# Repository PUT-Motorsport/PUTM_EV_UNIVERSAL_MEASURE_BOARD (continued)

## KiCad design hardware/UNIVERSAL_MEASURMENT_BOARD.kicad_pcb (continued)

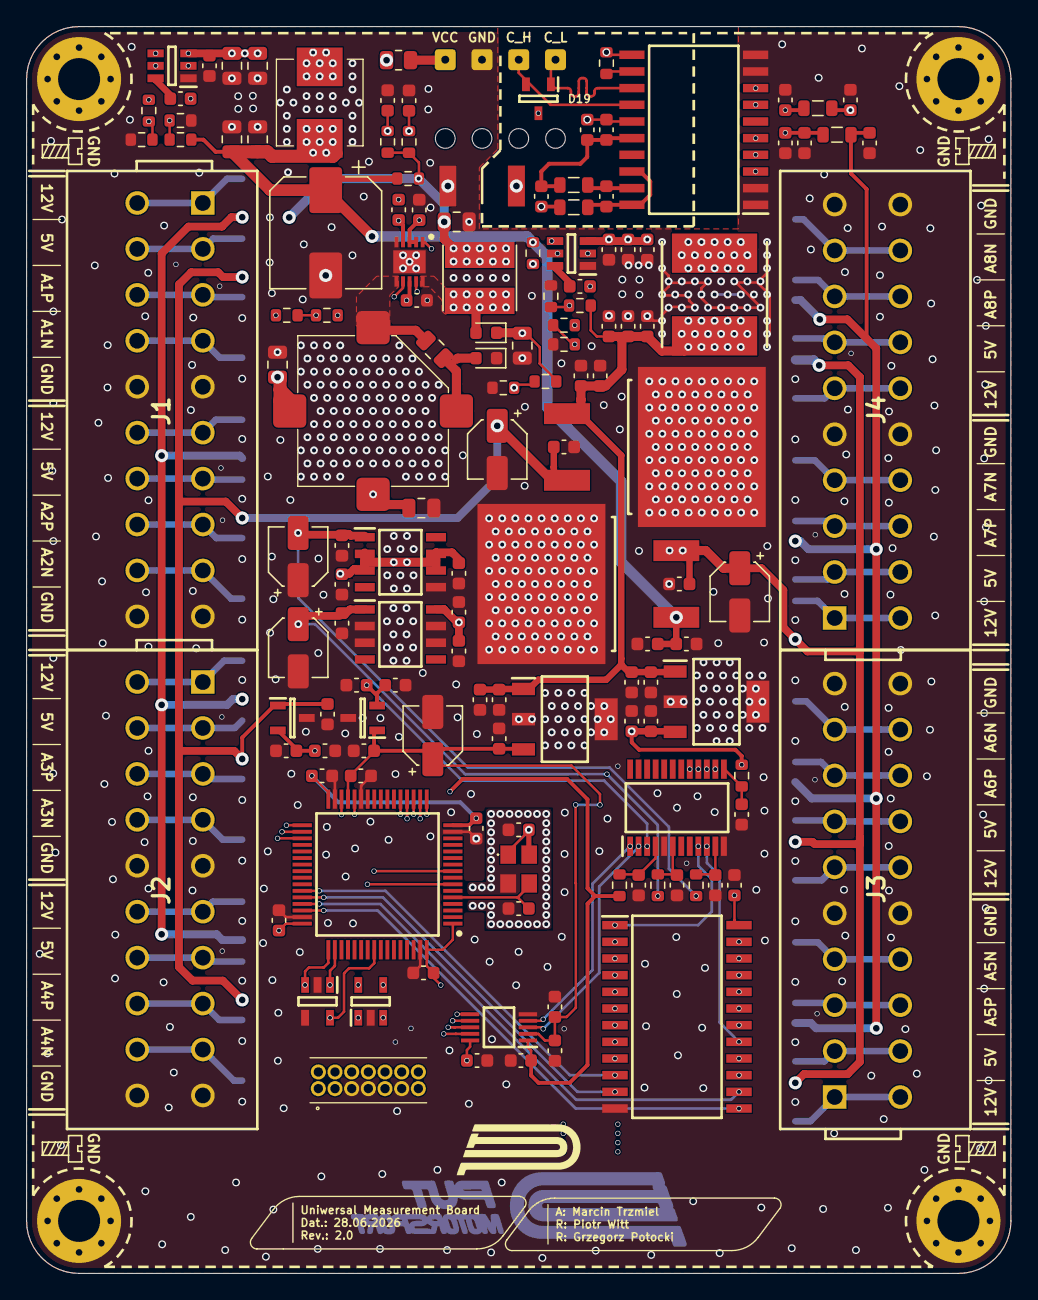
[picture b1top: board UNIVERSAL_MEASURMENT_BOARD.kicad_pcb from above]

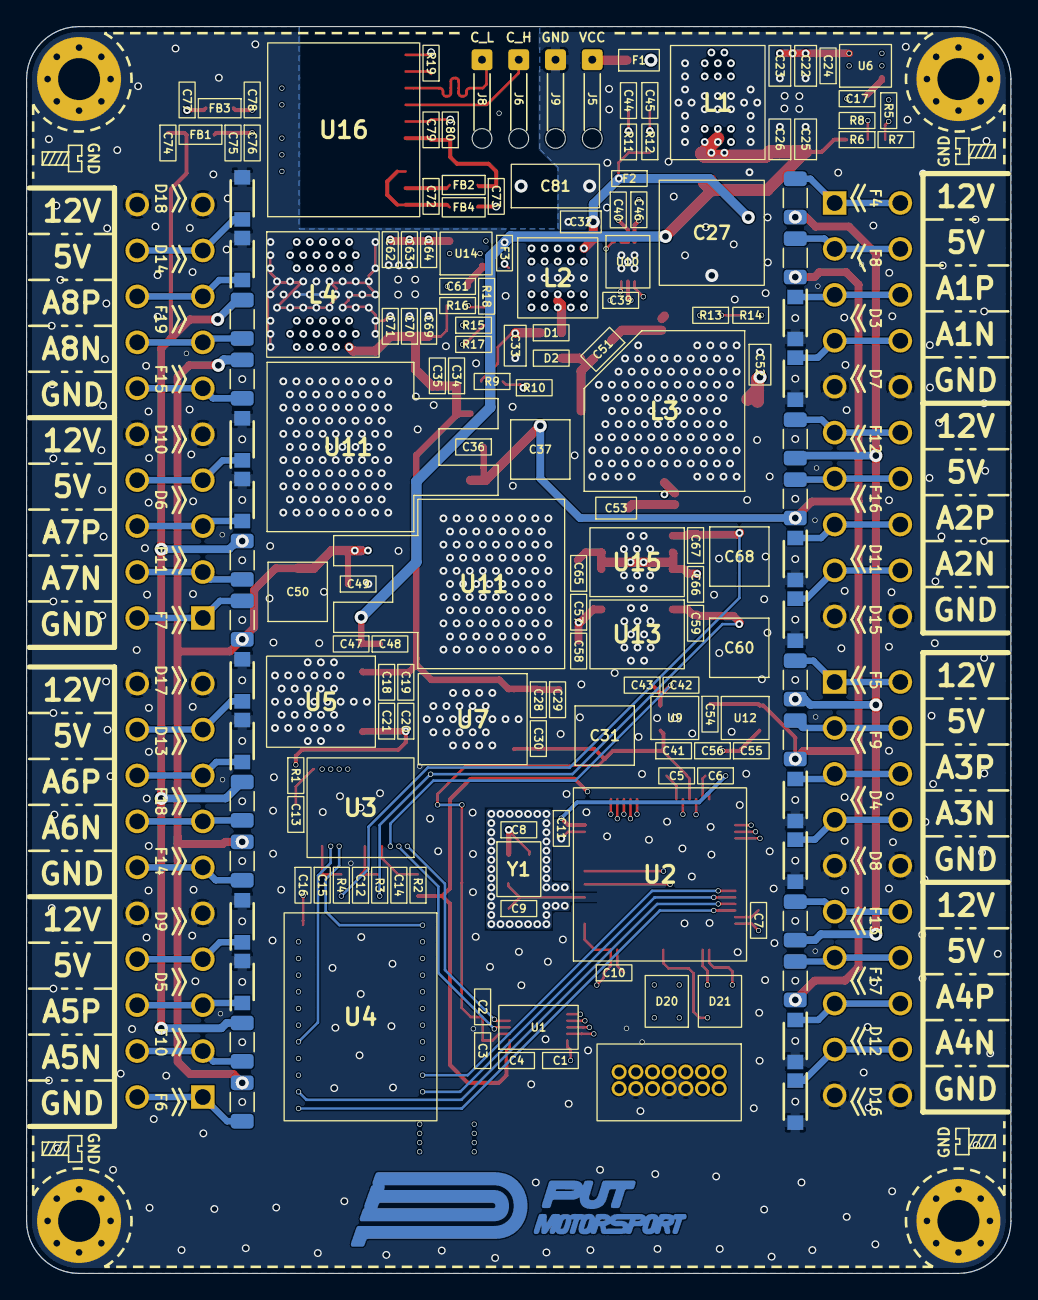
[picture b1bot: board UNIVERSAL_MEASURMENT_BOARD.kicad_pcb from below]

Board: 6 copper layers, 75.0 x 95.0 mm, 173 parts (36 on the bottom side), 101 nets.

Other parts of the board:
C1, C2, C4, C5, C6, C7, C8, C10, C11: 100nF; C_0603_1608Metric
C3: 10nF; C_0603_1608Metric
C9: 10pF; C_0603_1608Metric
U1: ADS8863IDGS; SOP50P490X110-10N
U2: STM32G484RET3; QFP50P1200X1200X160-64N
Y1: ATX-H11-F-16.000MHz-G100-T; ATXH11F16000MHzG100T

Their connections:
+3V0A: C4.1, U1.1 (REF), U2.28 (VREF+); also elsewhere on the board
+3V3: C1.1, C6.1, C7.1, C8.1, C10.1, C11.1, U1.10 (DVDD), U2.1 (VBAT), U2.16 (VDD), U2.32 (VDD), U2.48 (VDD), U2.64 (VDD), Y1.1 (~INH), Y1.4 (VDD); also elsewhere on the board
+3V3A: C2.1, C3.1, C5.1, U1.2 (AVDD), U2.29 (VDDA); also elsewhere on the board
/can/CAN_RX: U2.35 (FDCAN2_TX); also elsewhere on the board
/can/CAN_STB: U2.33 (PB11); also elsewhere on the board
/can/CAN_TX: U2.34 (FDCAN2_RX); also elsewhere on the board
/connectors/NRST: U2.7 (PG10); also elsewhere on the board
/connectors/SWCLK: U2.50 (SYS_JTCK-SWCLK); also elsewhere on the board
/connectors/SWDIO: U2.49 (SYS_JTMS-SWDIO); also elsewhere on the board
/connectors/SWO: U2.56 (SYS_JTDO-SWO); also elsewhere on the board
/connectors/UART_RX_PROG: U2.30 (LPUART1_RX); also elsewhere on the board
/connectors/UART_TX_PROG: U2.9 (LPUART1_TX); also elsewhere on the board
/mcu & adc/ADCCS: U1.6 (~CS), U2.18 (PA4)
/mcu & adc/ADDR1: U2.43 (PA9); also elsewhere on the board
/mcu & adc/ADDR2: U2.44 (PA10); also elsewhere on the board
/mcu & adc/ADDR3: U2.45 (PA11); also elsewhere on the board
/mcu & adc/AINN: U1.4 (AINN); also elsewhere on the board
/mcu & adc/AINP: U1.3 (AINP); also elsewhere on the board
/mcu & adc/HSE: C9.1, U2.5 (RCC_OSC_IN), Y1.3 (OUTPUT)
/mcu & adc/MISO: U1.9 (MISO), U2.20 (SPI1_MISO); also elsewhere on the board
/mcu & adc/MOSI: U1.7 (MOSI), U2.21 (SPI1_MOSI); also elsewhere on the board
/mcu & adc/MUXEN: U2.46 (PA12); also elsewhere on the board
/mcu & adc/PGACS: U2.17 (PA3); also elsewhere on the board
/mcu & adc/SCLK: U1.8 (SCLK), U2.19 (SPI1_SCK); also elsewhere on the board
GND: C1.2, C2.2, C3.2, C4.2, C5.2, C6.2, C7.2, C8.2, C9.2, C10.2, C11.2, U1.5 (GND), U2.15 (VSS), U2.27 (VSSA), U2.31 (VSS), U2.47 (VSS), U2.63 (VSS), Y1.2 (GND); also elsewhere on the board

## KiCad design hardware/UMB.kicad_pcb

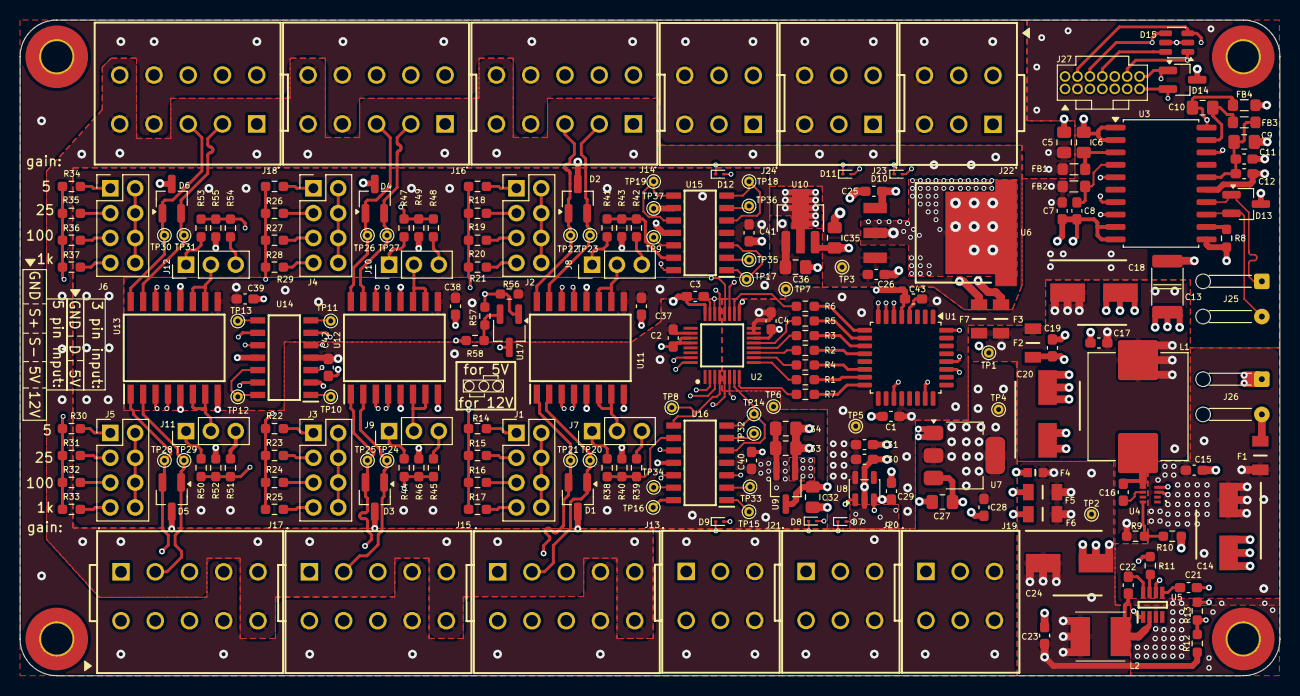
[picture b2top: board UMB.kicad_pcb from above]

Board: 6 copper layers, 128.8 x 67.0 mm, 214 parts (0 on the bottom side), 149 nets.

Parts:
C1, C2, C4, C7, C11, C15, C16, C19, C22, C30, C37, C38, C39, C40, C41, C42, C43: 100n; C_0603_1608Metric_Pad1.08x0.95mm_HandSolder
C3, C29, C31: 1u; C_0603_1608Metric_Pad1.08x0.95mm_HandSolder
C5, C6, C9, C10: 47u; C_0805_2012Metric_Pad1.18x1.45mm_HandSolder
C8, C12: 10n; C_0603_1608Metric_Pad1.08x0.95mm_HandSolder
C13: 4.7nF/Y2; CAPC5728X280N
C14, C18, C20, C24: 10u; CAPAE660X600N
C17, C23, C26, C28: 22u; C_0603_1608Metric_Pad1.08x0.95mm_HandSolder
C21: 8.2n; C_0603_1608Metric_Pad1.08x0.95mm_HandSolder
C25: 470n; C_0603_1608Metric_Pad1.08x0.95mm_HandSolder
C27, C33: 10u; C_0805_2012Metric_Pad1.18x1.45mm_HandSolder
C32, C34, C35, C36: 2.2u; C_0805_2012Metric_Pad1.18x1.45mm_HandSolder
D1, D2, D3, D4, D5, D6: CPDT-12V; SOT-23_Handsoldering
D7, D8, D9, D10, D11, D12: SZESD9101P2T5G; D_SOD-923
D13, D14: STS232050B751; SOT-23_Handsoldering
D15: 3.6V/400W; SOT-23-6
F1, F2: 3 A; FUSC3215X66N
F3: 1 A; FUSC3215X66N
F4: 800 mA; FUSC1608X55N
F5, F6: 375 mA; FUSC3215X66N
F7: 200 mA; FUSC3215X66N
FB1, FB2, FB3, FB4: 2K@100MHz; L_0805_2012Metric_Pad1.05x1.20mm_HandSolder
H1, H2, H3, H4: MountingHole_Pad; MountingHole_3.2mm_M3_Pad_TopBottom
J1, J2, J3, J4, J5, J6: PH2-04-UA; PinHeader_2x04_P2.54mm_Vertical
J7, J8, J9, J10, J11, J12: PH1-03-UA; PinHeader_1x03_P2.54mm_Vertical
J13, J14, J15, J16, J17, J18: Conn_01x05; 26011105
J19, J20, J21, J22, J23, J24: Conn_01x03; 26011103
J25, J26: Conn_01x02; Wire_StrainRelief
J27: FTSH-107-01-L-D-K; FTSH-107-XX-YYY-D-K
L1: 15uH; L_APV_APH1040
L2: 6.8uH; VLS5045EX330M
R1, R2, R3, R4, R5, R6, R7: 47R; R_0603_1608Metric_Pad0.98x0.95mm_HandSolder
R8: 100k; R_0603_1608Metric_Pad0.98x0.95mm_HandSolder
R9: 174k; R_0603_1608Metric_Pad0.98x0.95mm_HandSolder
R10, R11, R13: 10.2k; R_0603_1608Metric_Pad0.98x0.95mm_HandSolder
R12: 84.5k; R_0603_1608Metric_Pad0.98x0.95mm_HandSolder
R14, R18, R22, R26, R30, R34: 12.4k; R_0603_1608Metric_Pad0.98x0.95mm_HandSolder
R15, R19, R23, R27, R31, R35, R56: 2.1k; R_0603_1608Metric_Pad0.98x0.95mm_HandSolder
R16, R20, R24, R28, R32, R36: 499R; R_0603_1608Metric_Pad0.98x0.95mm_HandSolder
R17, R21, R25, R29, R33, R37: 49.9R; R_0603_1608Metric_Pad0.98x0.95mm_HandSolder
R38, R41, R44, R47, R50, R53, R57: 14k; R_0603_1608Metric_Pad0.98x0.95mm_HandSolder
R39, R42, R45, R48, R51, R54: 0R; R_0603_1608Metric_Pad0.98x0.95mm_HandSolder
R40, R43, R46, R49, R52, R55, R58: 10k; R_0603_1608Metric_Pad0.98x0.95mm_HandSolder
TP1, TP2, TP3, TP4, TP5, TP6, TP7, TP8, TP9, TP10, TP11, TP12, TP13, TP14, TP15, TP16, TP17, TP18, TP19, TP20, TP21, TP22, TP23, TP24, TP25, TP26, TP27, TP28, TP29, TP30, TP31, TP32, TP33, TP34, TP35, TP36, TP37: TestPoint_Small; TestPoint_THTPad_D1.0mm_Drill0.5mm
U1: STM32G0C1KCTxN; LQFP-32_7x7mm_P0.8mm
U2: ADS114S08BIPBSR; QFP50P700X700X120-32N
U3: ADM3057ExRW; SOIC-20W_7.5x12.8mm_P1.27mm
U4: TPS563300DRLR; TPS62932DRLR
U5: TPS563219ADDFR; SOT65P280X110-8N
U6: LM2940CS-12/NOPB; KTT0003B
U7: LM1117IMP-5.0; SOT-223-3_TabPin2
U8: TPS7B92033DBVR; SOT-23-5
U9: AP2127N3-1.5; TSOT-23_HandSoldering
U10: LDK320ADU120R; SOT-89-3_Handsoldering
U11, U12, U13: INA2128UA_1K; SOIC127P1030X265-16N
U14, U15, U16: TLC274AIDR; SOIC127P600X175-14N
U17: TL431LIBQDBZRQ1; SOT-23W_Handsoldering

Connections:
+3.3V: C1.1, C4.1, C7.1, C30.1, C31.1, C43.1, FB2.2, J27.3, TP5.1, U1.4 (VDD), U1.20 (VDD), U2.15 (IOVDD), U2.16 (DVDD), U8.5 (OUT)
+5V: C5.2, C28.1, FB1.2, J13.4, J14.4, J15.4, J16.4, J17.4, J18.4, J19.3, J20.3, J21.3, J22.3, J23.3, J24.3, TP4.1, U7.2 (VO)
+5VA: C2.1, C33.1, C34.1, C40.1, C41.1, C42.1, TP6.1, U2.26 (AVDD), U9.2 (VO), U14.4 (V+), U15.4 (V+), U16.4 (V+)
+6VA: R56.1, R57.1, U11.5 (REFA), U11.12 (REFB), U12.5 (REFA), U12.12 (REFB), U13.5 (REFA), U13.12 (REFB), U17.1 (K)
+7V: C23.1, C24.1, F4.1, F5.1, F6.1, L2.2, R12.1, TP2.1
+12V: C26.1, J13.5, J14.5, J15.5, J16.5, J17.5, J18.5, TP3.1, U6.3 (OUT)
+12VA: C36.1, C37.2, C38.2, C39.2, R56.2, TP7.1, U10.1 (OUT), U11.9 (V+), U12.9 (V+), U13.9 (V+)
+14.5V: C17.1, C18.1, F2.1, F3.1, F7.1, L1.2, R9.2, TP1.1
+24V: F1.1, J26.2
/ADC/ADC_DRDY: R5.2, U2.13 (~DRDY)
/ADC/ADC_RST: R6.2, U2.18 (~RESET)
/ADC/ADC_SPI.CLK: R2.2, U2.11 (SCLK)
/ADC/ADC_SPI.MISO: R3.2, U2.12 (DOUT/~DRDY)
/ADC/ADC_SPI.MOSI: R4.2, U2.10 (DIN)
/ADC/ADC_SPI.NSS: R1.2, U2.9 (~CS)
/ADC/ADC_START: R7.2, U2.8 (START/SYNC)
/ADC/DIF1: TP8.1, U2.4 (AIN3), U16.8, U16.10 (+)
/ADC/DIF2: TP9.1, U2.21 (GPIO1/AIN9), U15.12 (+), U15.14
/ADC/DIF3: TP10.1, U2.2 (AIN5), U14.1, U14.3 (+)
/ADC/DIF4: TP11.1, U2.32 (REFP1/AIN6), U14.5 (+), U14.7
/ADC/DIF5: TP12.1, U2.3 (AIN4), U14.12 (+), U14.14
/ADC/DIF6: TP13.1, U2.31 (REFN1/AIN7), U14.8, U14.10 (+)
/ADC/SE1: TP14.1, U2.7 (AIN0), U16.5 (+), U16.7
/ADC/SE2: TP15.1, U2.6 (AIN1), U16.1, U16.3 (+)
/ADC/SE3: TP16.1, U2.5 (AIN2), U16.12 (+), U16.14
/ADC/SE4: TP17.1, U2.19 (GPIO3/AIN11), U15.1, U15.3 (+)
/ADC/SE5: TP18.1, U2.20 (GPIO2/AIN10), U15.5 (+), U15.7
/ADC/SE6: TP19.1, U2.22 (GPIO0/AIN8), U15.8, U15.10 (+)
/Analog/DIF1+: D1.1 (A1), J13.2, TP20.1, U11.2 (V+INA)
/Analog/DIF1-: D1.2 (A2), J13.3, TP21.1, U11.1 (V-INA)
/Analog/DIF1_12: J7.2, U11.6 (VOA), U11.7 (SENSEA)
/Analog/DIF2+: D2.2 (A2), J14.2, TP23.1, U11.15 (V+INB)
/Analog/DIF2-: D2.1 (A1), J14.3, TP22.1, U11.16 (V-INB)
/Analog/DIF2_12: J8.2, U11.10 (SENSEB), U11.11 (VOB)
/Analog/DIF3+: D3.1 (A1), J15.2, TP24.1, U12.2 (V+INA)
/Analog/DIF3-: D3.2 (A2), J15.3, TP25.1, U12.1 (V-INA)
/Analog/DIF3_12: J9.2, U12.6 (VOA), U12.7 (SENSEA)
/Analog/DIF4+: D4.2 (A2), J16.2, TP27.1, U12.15 (V+INB)
/Analog/DIF4-: D4.1 (A1), J16.3, TP26.1, U12.16 (V-INB)
/Analog/DIF4_12: J10.2, U12.10 (SENSEB), U12.11 (VOB)
/Analog/DIF5+: D5.1 (A1), J17.2, TP29.1, U13.2 (V+INA)
/Analog/DIF5-: D5.2 (A2), J17.3, TP28.1, U13.1 (V-INA)
/Analog/DIF5_12: J11.2, U13.6 (VOA), U13.7 (SENSEA)
/Analog/DIF6+: D6.2 (A2), J18.2, TP31.1, U13.15 (V+INB)
/Analog/DIF6-: D6.1 (A1), J18.3, TP30.1, U13.16 (V-INB)
/Analog/DIF6_12: J12.2, U13.10 (SENSEB), U13.11 (VOB)
/Analog/RGA1_1: R14.2, R15.2, R16.2, R17.2, U11.3 (RGA_1)
/Analog/RGA1_2: J1.2 (Pin_8), J1.4 (Pin_7), J1.6, J1.8 (Pin_5), U11.4 (RGA_2)
/Analog/RGA2_1: R18.2, R19.2, R20.2, R21.2, U11.14 (RGB_2)
/Analog/RGA2_2: J2.2 (Pin_8), J2.4 (Pin_7), J2.6, J2.8 (Pin_5), U11.13 (RGB_1)
/Analog/RGA3_1: R22.2, R23.2, R24.2, R25.2, U12.3 (RGA_1)
/Analog/RGA3_2: J3.2 (Pin_8), J3.4 (Pin_7), J3.6, J3.8 (Pin_5), U12.4 (RGA_2)
/Analog/RGA4_1: R26.2, R27.2, R28.2, R29.2, U12.14 (RGB_2)
/Analog/RGA4_2: J4.2 (Pin_8), J4.4 (Pin_7), J4.6, J4.8 (Pin_5), U12.13 (RGB_1)
/Analog/RGA5_1: R30.2, R31.2, R32.2, R33.2, U13.3 (RGA_1)
/Analog/RGA5_2: J5.2 (Pin_8), J5.4 (Pin_7), J5.6, J5.8 (Pin_5), U13.4 (RGA_2)
/Analog/RGA6_1: R34.2, R35.2, R36.2, R37.2, U13.14 (RGB_2)
/Analog/RGA6_2: J6.2 (Pin_8), J6.4 (Pin_7), J6.6, J6.8 (Pin_5), U13.13 (RGB_1)
/CAN/CAN+: D13.1 (A1), J25.1, U3.14 (CANH)
/CAN/CAN-: D13.2 (A2), J25.2, U3.13 (CANL)
/CAN/CAN_RX: U1.32 (FDCAN1_RX), U3.5 (RXD)
/CAN/CAN_STBY: U1.28 (PD2), U3.8 (STBY)
/CAN/CAN_TX: U1.27 (FDCAN1_TX), U3.7 (TXD)
/CAN/GND_CAN_ISO: C9.1, C11.1, C12.2, C13.2, D13.3 (common), FB4.1, R8.2, U3.11 (GND2), U3.15 (GND2)
/Connectors/NRST: D15.1 (K), J27.12, U1.6 (PF2)
/Connectors/SWCLK: D15.4 (K), J27.6, U1.7 (PA0)
/Connectors/SWDIO: D15.3 (K), J27.4, U1.8 (PA1)
/Connectors/SWO: D15.6 (K), J27.8
/Connectors/UART_RX: D14.2 (A2), J27.13, U1.23 (USART1_RX (PA10))
/Connectors/UART_TX: D14.1 (A1), J27.14, U1.19 (USART1_TX (PA9))
GND: C1.2, C2.2, C3.1, C4.2, C5.1, C6.1, C7.2, C8.2, C13.1, C14.2, C15.2, C17.2, C18.2, C19.2, C20.2, C21.2, C23.2, C24.2, C25.2, C26.2, C27.2, C28.2, C29.2, C30.2, C31.2, C32.2, C33.2, C34.2, C35.2, C36.2, C37.1, C38.1, C39.1, C40.2, C41.2, C42.2, C43.2, D1.3 (common), D2.3 (common), D3.3 (common), D4.3 (common), D5.3 (common), D6.3 (common), D7.2 (A2), D8.2 (A2), D9.2 (A2), D10.2 (A2), D11.2 (A2), D12.2 (A2), D14.3 (common), D15.2 (A), D15.5 (K), H1.1, H2.1, H3.1, H4.1, J13.1, J14.1, J15.1, J16.1, J17.1, J18.1, J19.1, J20.1, J21.1, J22.1, J23.1, J24.1, J26.1, J27.5, J27.7, J27.11, R10.2, R13.2, R40.2, R43.2, R46.2, R49.2, R52.2, R55.2, R58.2, U1.5 (VSS), U2.14 (DGND), U2.17 (CLK), U2.24 (REFCOM), U2.27 (AVSS_1), U2.28 (AVSS_2), U3.1 (GND1), U3.2 (GND1), U3.9 (AUXIN), U3.10 (GND1), U4.4 (GND), U5.1 (GND), U6.2 (GND), U7.1 (GND), U8.2 (GND), U9.1 (GND), U10.2 (GND), U11.8 (V-), U12.8 (V-), U13.8 (V-), U14.11 (V-), U15.11 (V-), U16.11 (V-), U17.3 (A)
unnamed: C10.1, FB4.2, U3.18 (GNDISO), U3.20 (GNDISO)
unnamed: J1.1, R14.1
unnamed: J1.3 (Pin_2), R15.1
unnamed: J1.5 (Pin_3), R16.1
unnamed: J1.7 (Pin_4), R17.1
unnamed: J2.1, R18.1
unnamed: J2.3 (Pin_2), R19.1
unnamed: J2.5 (Pin_3), R20.1
unnamed: J2.7 (Pin_4), R21.1
unnamed: J3.1, R22.1
unnamed: J3.3 (Pin_2), R23.1
unnamed: J3.5 (Pin_3), R24.1
unnamed: J3.7 (Pin_4), R25.1
unnamed: J4.1, R26.1
unnamed: J4.3 (Pin_2), R27.1
unnamed: J4.5 (Pin_3), R28.1
unnamed: J4.7 (Pin_4), R29.1
unnamed: J5.1, R30.1
unnamed: J5.3 (Pin_2), R31.1
unnamed: J5.5 (Pin_3), R32.1
unnamed: J5.7 (Pin_4), R33.1
unnamed: J6.1, R34.1
unnamed: J6.3 (Pin_2), R35.1
unnamed: J6.5 (Pin_3), R36.1
unnamed: J6.7 (Pin_4), R37.1
unnamed: J7.1, R38.2
unnamed: J7.3, R39.1
unnamed: J8.1, R41.2
unnamed: J8.3, R42.1
unnamed: J9.1, R44.2
unnamed: J9.3, R45.1
unnamed: J10.1, R47.2
unnamed: J10.3, R48.1
unnamed: J11.1, R50.2
unnamed: J11.3, R51.1
unnamed: J12.1, R53.2
unnamed: J12.3, R54.1
unnamed: R6.1, U1.9 (PA2)
unnamed: R5.1, U1.10 (PA3)
unnamed: R3.1, U1.11 (SPI1_NSS)
unnamed: R2.1, U1.12 (SPI1_SCK)
unnamed: R4.1, U1.14 (SPI1_MOSI)
unnamed: R1.1, U1.15 (PB0)
unnamed: R7.1, U1.16 (PB1)
unnamed: C3.2, U2.23 (REFOUT)
unnamed: R8.1, U3.12 (RS)
unnamed: C6.2, FB1.1, U3.3 (VCC)
unnamed: C8.1, FB2.1, U3.4 (VIO)
unnamed: C9.2, C11.2, C12.1, FB3.1, U3.16 (VISOIN)
unnamed: C10.2, FB3.2, U3.19 (VISOOUT)
unnamed: C16.2, U4.6 (BST)
unnamed: R9.1, R10.1, U4.8 (FB)
unnamed: C16.1, L1.1, U4.5 (SW)
unnamed: C14.1, C15.1, F1.2, U4.3 (VIN)
unnamed: R11.2, U5.7 (EN)
unnamed: C21.1, U5.5 (SS)
unnamed: C22.2, L2.1, U5.2 (SW)
unnamed: C22.1, U5.8 (VBST)
unnamed: R12.2, R13.1, U5.6 (VFB)
unnamed: C19.1, C20.1, F2.2, R11.1, U5.3 (VIN)
unnamed: C25.1, F3.2, U6.1 (IN)
unnamed: C27.1, F4.2, U7.3 (VI)
unnamed: C29.1, F5.2, U8.1 (IN), U8.3 (EN)
unnamed: C32.1, F6.2, U9.3 (VI)
unnamed: C35.1, F7.2, U10.3 (IN)
unnamed: R44.1, R45.2, R46.1, U14.2 (-)
unnamed: R47.1, R48.2, R49.1, U14.6 (-)
unnamed: R53.1, R54.2, R55.1, U14.9 (-)
unnamed: R50.1, R51.2, R52.1, U14.13 (-)
unnamed: R41.1, R42.2, R43.1, U15.13 (-)
unnamed: R38.1, R39.2, R40.1, U16.9 (-)
unnamed: R57.2, R58.1, U17.2 (REF)
SE1IN: D7.1 (A1), J19.2, TP32.1, U16.6 (-)
SE2IN: D8.1 (A1), J20.2, TP33.1, U16.2 (-)
SE3IN: D9.1 (A1), J21.2, TP34.1, U16.13 (-)
SE4IN: D10.1 (A1), J22.2, TP35.1, U15.2 (-)
SE5IN: D11.1 (A1), J23.2, TP36.1, U15.6 (-)
SE6IN: D12.1 (A1), J24.2, TP37.1, U15.9 (-)

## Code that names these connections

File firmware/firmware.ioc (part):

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Mcu.Name=STM32G0C1K(C-E)TxN
Mcu.Package=LQFP32
Mcu.UserName=STM32G0C1KCTxN
PA10\ [PA12].Mode=Asynchronous
PA10\ [PA12].Signal=USART1_RX
PA11\ [PA9].GPIOParameters=GPIO_Label
PA11\ [PA9].GPIO_Label=CAN_RX
PA11\ [PA9].Mode=FDCAN_Activate
PA11\ [PA9].Signal=FDCAN1_RX
PA13.Mode=Serial_Wire
PA13.Signal=SYS_SWDIO
PA14-BOOT0.Mode=Serial_Wire
PA14-BOOT0.Signal=SYS_SWCLK
PA2.GPIOParameters=PinState,GPIO_PuPd,GPIO_Label
PA2.GPIO_Label=ADC_RST
PA2.GPIO_PuPd=GPIO_PULLUP
PA2.PinState=GPIO_PIN_SET
PA2.Signal=GPIO_Output
PA3.GPIOParameters=GPIO_Label,GPIO_ModeDefaultEXTI
PA3.GPIO_Label=ADC_DRDY
PA3.GPIO_ModeDefaultEXTI=GPIO_MODE_IT_FALLING
PA3.Signal=GPXTI3
PA5.GPIOParameters=GPIO_Label
PA5.GPIO_Label=ADC_SPI_SCK
PA5.Mode=Full_Duplex_Master
PA5.Signal=SPI1_SCK
PA6.GPIOParameters=GPIO_Label
PA6.GPIO_Label=ADC_SPI_MISO
PA6.Mode=Full_Duplex_Master
PA6.Signal=SPI1_MISO
PA7.GPIOParameters=GPIO_Label
PA7.GPIO_Label=ADC_SPI_MOSI
PA7.Mode=Full_Duplex_Master
PA7.Signal=SPI1_MOSI
PA9.Mode=Asynchronous
PA9.Signal=USART1_TX
PB0.GPIOParameters=GPIO_PuPd,GPIO_Label
PB0.GPIO_Label=ADC_SPI_CS
PB0.GPIO_PuPd=GPIO_PULLDOWN
PB0.Signal=GPIO_Output
PB1.GPIOParameters=GPIO_PuPd,GPIO_Label
PB1.GPIO_Label=ADC_START
PB1.GPIO_PuPd=GPIO_PULLDOWN
PB1.Signal=GPIO_Output
PD1.GPIOParameters=GPIO_Label
PD1.GPIO_Label=CAN_TX
PD1.Mode=FDCAN_Activate
PD1.Signal=FDCAN1_TX
PD2.GPIOParameters=GPIO_PuPd,GPIO_Label
PD2.GPIO_Label=CAN_STBY
PD2.GPIO_PuPd=GPIO_PULLDOWN
PD2.Signal=GPIO_Output
RCC.HSE_VALUE=8000000
RCC.SYSCLKFreq_VALUE=64000000
RCC.SYSCLKSource=RCC_SYSCLKSOURCE_PLLCLK
board=custom

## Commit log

2025-11-25 Create a
2025-12-09 Deleted hardware/upp_1
2025-12-09 Deleted hardware/upp_simple
2025-12-09 Cleaned up
2025-12-16 Solved ERC errors and cleaned up schematic
2026-01-27 Changed Opamps cleared schematic
2026-02-03 All done except power
2026-02-03 continued
2026-02-09 Power section done
2026-02-11 schematic review corrections
2026-02-11 final schematic review corrections
2026-02-12 Added all footprints and parts Mouser IDs
2026-02-18 DC/DC conv documentation, annotation cleanup and footprints correction
2026-02-18 added pdf
2026-02-22 Preliminary components placement
2026-02-24 added footprints
2026-02-24 added part list and calculation sheet for DC/DC converters
2026-03-04 Finished components placement on PCB
2026-03-09 Finished routing on PCB
2026-03-10 Added all missing datasheet links etc
2026-03-13 Corrections after review
2026-03-15 Added description, fixed engineering fee
2026-03-17 Vias on pad and traces under components fix
2026-03-17 Added Voltage reference, fixed silkscreen and BOM
2026-03-19 Fixed R57 value
2026-03-19 Changed some components - they were non stocked
2026-03-19 Added PUTM logo and gerber files
2026-03-21 first outcom of pcb design
2026-03-24 Footprints files cleanup
2026-03-24 Review fixes
2026-03-25 Additional review fixes
2026-03-26 solved DRC problems
2026-03-26 Solved ERC problems
2026-03-26 clean up project visuals
2026-03-27 Added some documentation files
2026-04-09 created cubemx project
2026-04-12 pinout and peripherals init
2026-04-12 can initialization
2026-04-14 added adc registers and commands
2026-04-15 added timer for ads spi delay
2026-04-15 exported ads drivers to external library
2026-04-15 added external interrupt for drdy input
2026-04-15 added read data function
2026-04-15 divided ads driver library into two files
2026-04-15 added initialization in main, fixed register values
2026-04-15 added ads pin config
2026-04-16 added utility functions for pga config and datarate
2026-04-17 added data read in interrupt
2026-04-18 Set up interfaces and generated base code using CubeMX
2026-04-20 added class for ads driver
2026-04-20 fixed pinout
2026-04-24 Fixed VOUT range of PGA to 3.0V, fixed GPIO connection between FDCAN and MCU, added 1.5V VREF to PGA, changed value of enable divider of 7V DCDC converter.
2026-04-25 Schematic: changed fuse values in measurement sections and in the ±18V converter, changed the value of the CAN safety capacitor, corrected the marking of the programming TVS diode, corrected schemati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
2026-04-25 Reduced PCB dimensions, working on power section
2026-04-27 Add CAN interface to PCB, continue work on power section
2026-04-29 added reference selection to initialization
2026-04-29 Update power section:
    - Change input capacitor configuration to 1 per inductor in ±18V converter
    - Add ±18V DC/DC, 12V LDO, and 5V LDO layouts
    - Add TVS diodes and fuses to the measurement path
2026-04-30 Finalize power section layout:
    - Add dual 3.3V and ±15V LDOs
    - Add 3.0V and 1.5V references
    - Rework TVS and fuse placement in measurement path
    - Add thermal vias to LDOs and inductors
    - Improve component markings
2026-04-30 Update board:
    - Connect screw terminals to GND
    - Bump revision to 1.1
    - Add date marking on the board
2026-05-01 Fixed pinout errors & changed branch name
2026-05-04 fixed state transition
2026-05-04 fixed register read
2026-05-04 added write checking
2026-05-04 changed initialization
2026-05-04 added data readings structure
2026-05-05 fixed data write check bug
2026-05-06 changed adc readings structure to all-channel array
2026-05-09 Done board layout:
    - Add MCU, PGA, and ADC
    - Add programming port and TVSs
    - Add additional thermal vias to LDOs
2026-05-11 Finish PCB routing
2026-05-11 Solved ERC & DRC
2026-05-12 added channel configuration:
2026-05-13 simplified adc driver
2026-05-20 ADC Ref pins connection fix
2026-05-20 wrong commiting correction
2026-05-24 Review fix: rework feedback circuit of -18V converter
2026-06-01 added voltage reading
2026-06-02 extracted adc logic to upp file
2026-06-02 added uart logging
2026-06-04 hardware sync
2026-06-17 added differential channel voltage calculation
2026-06-18 added upp channel data frame
2026-06-19 added python script for reading upp output
2026-06-28 chore: solve additional DRC problem
2026-06-28 style: fix board visuals
2026-06-28 docs: update README and add visualization images
2026-06-28 chore: unify schematic module names
